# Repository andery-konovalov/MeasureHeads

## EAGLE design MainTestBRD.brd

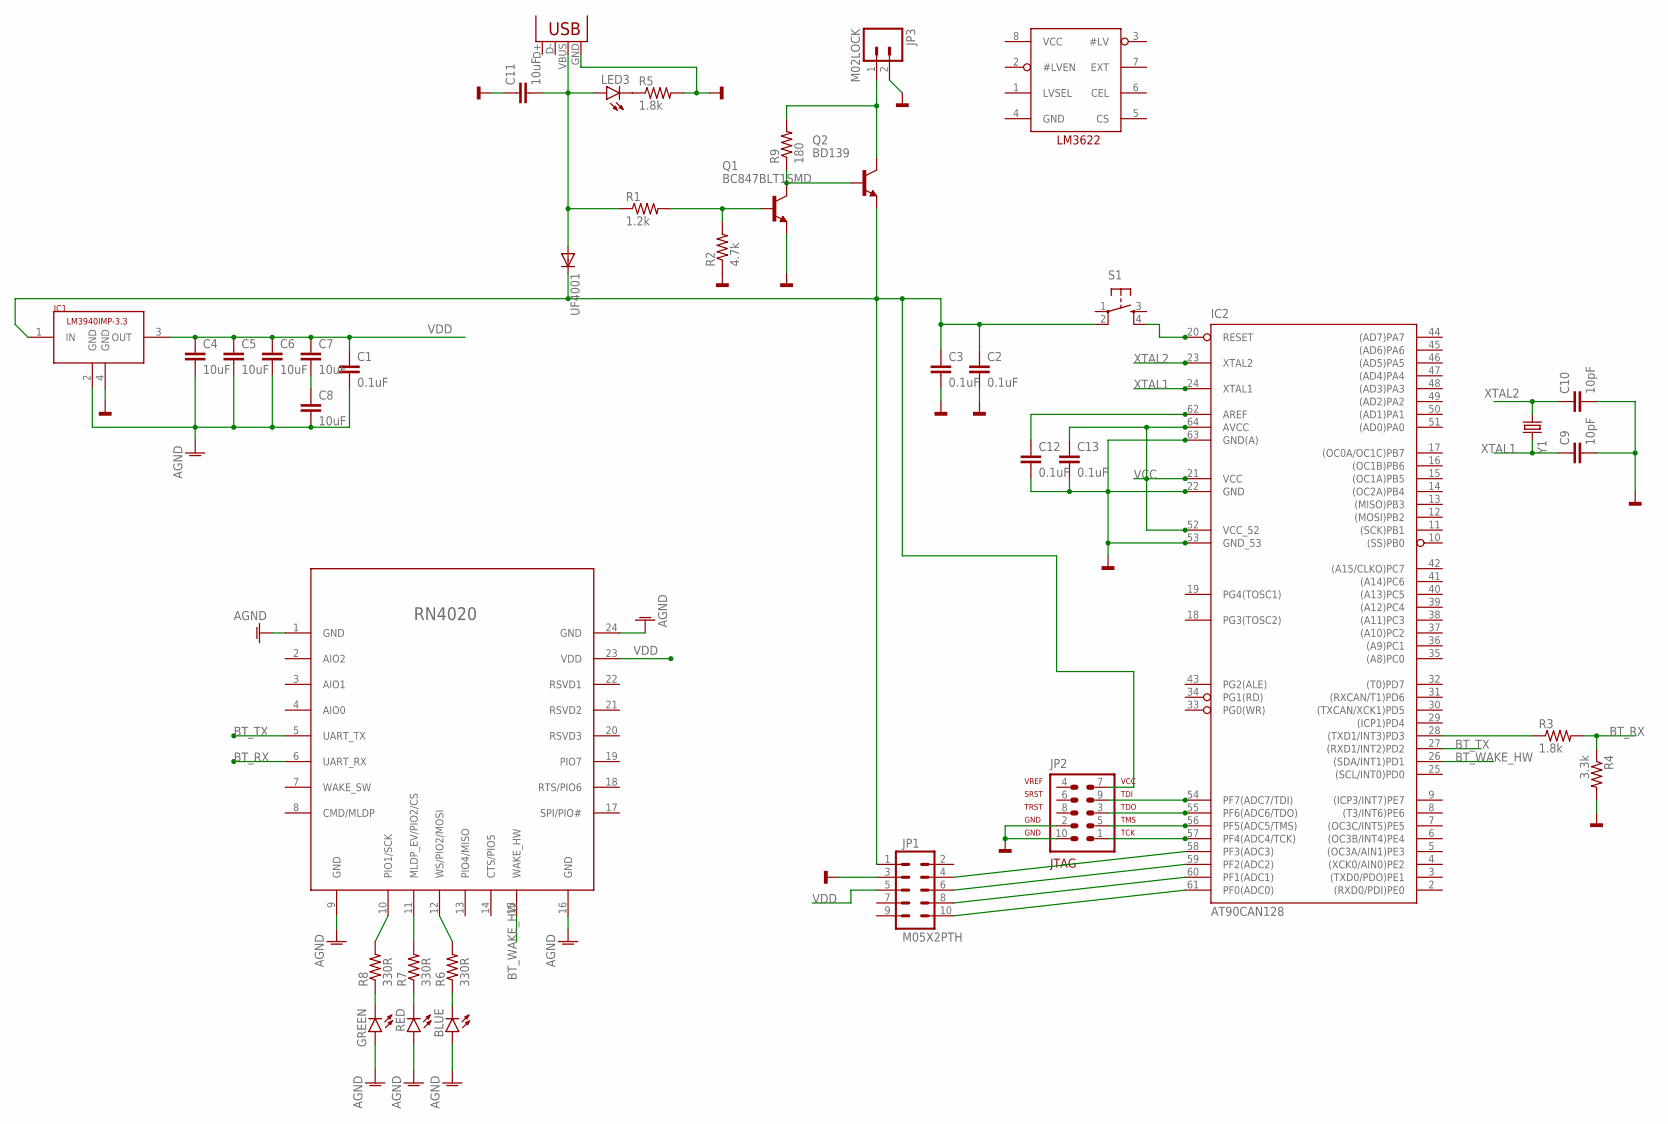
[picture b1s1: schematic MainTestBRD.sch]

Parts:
BLUE: LED1206; LED-1206
C1, C2, C3, C12, C13: 0.1uF; 1206
C4, C5, C6, C7, C8, C11: 10uF; 1206
C9, C10: 10pF; 1206
GREEN: LED1206; LED-1206
IC1: LM3940IMP-3.3; SOT223
IC2: AT90CAN128; TQFP64
JP1: M05X2PTH; AVR_ICSP
JP2: AVR-JTAG-10
JP3: M02LOCK; 1X02_LOCK
JP4: USB-B; USB-B-PTH
LED3: LED1206; LED-1206
Q1: BC847BLT1SMD; SOT23
Q2: BD139; TO126
R1: 1.2k; 0603-RES
R2: 4.7k; 0603-RES
R3, R5: 1.8k; 0603-RES
R4: 3.3k; 0603-RES
R6, R7, R8: 330R; 0603-RES
R9: 180; 0603-RES
RED: LED1206; LED-1206
S1: TAC_SWITCHPTH; TACTILE-PTH
U$1: LM3622; SO08
U$2: RN4020
UF4001: DIODE-DO41-7.6; DO41-7.6
Y1: CRYSTALHC49UV; HC49U-V

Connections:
AGND: BLUE.A, C1.2, C4.2, C5.2, C6.2, C8.2, GREEN.A, IC1.2 (GND), RED.A, U$2.1 (GND), U$2.9 (GND), U$2.16 (GND), U$2.24 (GND)
BT_RX: R3.2, R4.1, U$2.6 (UART_RX)
BT_TX: IC2.27 ((RXD1/INT2)PD2), U$2.5 (UART_TX)
BT_WAKE_HW: IC2.26 ((SDA/INT1)PD1), U$2.15 (WAKE_HW)
GND: C2.2, C3.2, C9.2, C10.2, C11.1, C12.2, C13.2, IC1.4 (GND), IC2.22 (GND), IC2.53 (GND_53), IC2.63 (GND(A)), JP1.3, JP2.2, JP2.10, JP3.2, JP4.GND, Q1.2 (E), R2.1, R4.2, R5.2
unnamed: R6.2, U$2.12 (WS/PIO2/MOSI)
unnamed: R8.2, U$2.10 (PIO1/SCK)
unnamed: IC2.28 ((TXD1/INT3)PD3), R3.1
unnamed: BLUE.C, R6.1
unnamed: R7.2, U$2.11 (MLDP_EV/PIO2/CS)
unnamed: IC2.57 (PF4(ADC4/TCK)), JP2.1
unnamed: R7.1, RED.C
unnamed: C7.2, C8.1
unnamed: IC2.56 (PF5(ADC5/TMS)), JP2.5
unnamed: GREEN.C, R8.1
unnamed: IC2.55 (PF6(ADC6/TDO)), JP2.3
unnamed: IC2.54 (PF7(ADC7/TDI)), JP2.9
unnamed: IC2.20 (RESET), S1.4
unnamed: Q1.1 (B), R1.2, R2.2
unnamed: C12.1, IC2.62 (AREF)
unnamed: IC2.61 (PF0(ADC0)), JP1.10
unnamed: C11.2, JP4.VBUS, LED3.A, R1.1, UF4001.A
unnamed: Q1.3 (C), Q2.3 (B), R9.1
unnamed: IC2.60 (PF1(ADC1)), JP1.8
unnamed: LED3.C, R5.1
unnamed: IC2.59 (PF2(ADC2)), JP1.6
unnamed: IC2.58 (PF3(ADC3)), JP1.4
unnamed: JP3.1, Q2.2 (C), R9.2
VCC: C2.1, C3.1, C13.1, IC1.1 (IN), IC2.21 (VCC), IC2.52 (VCC_52), IC2.64 (AVCC), JP1.1, JP2.7, S1.2, UF4001.C
VDD: C1.1, C4.1, C5.1, C6.1, C7.1, IC1.3 (OUT), JP1.5, U$2.23 (VDD)
XTAL1: C9.1, IC2.24 (XTAL1), Y1.2
XTAL2: C10.1, IC2.23 (XTAL2), Y1.1

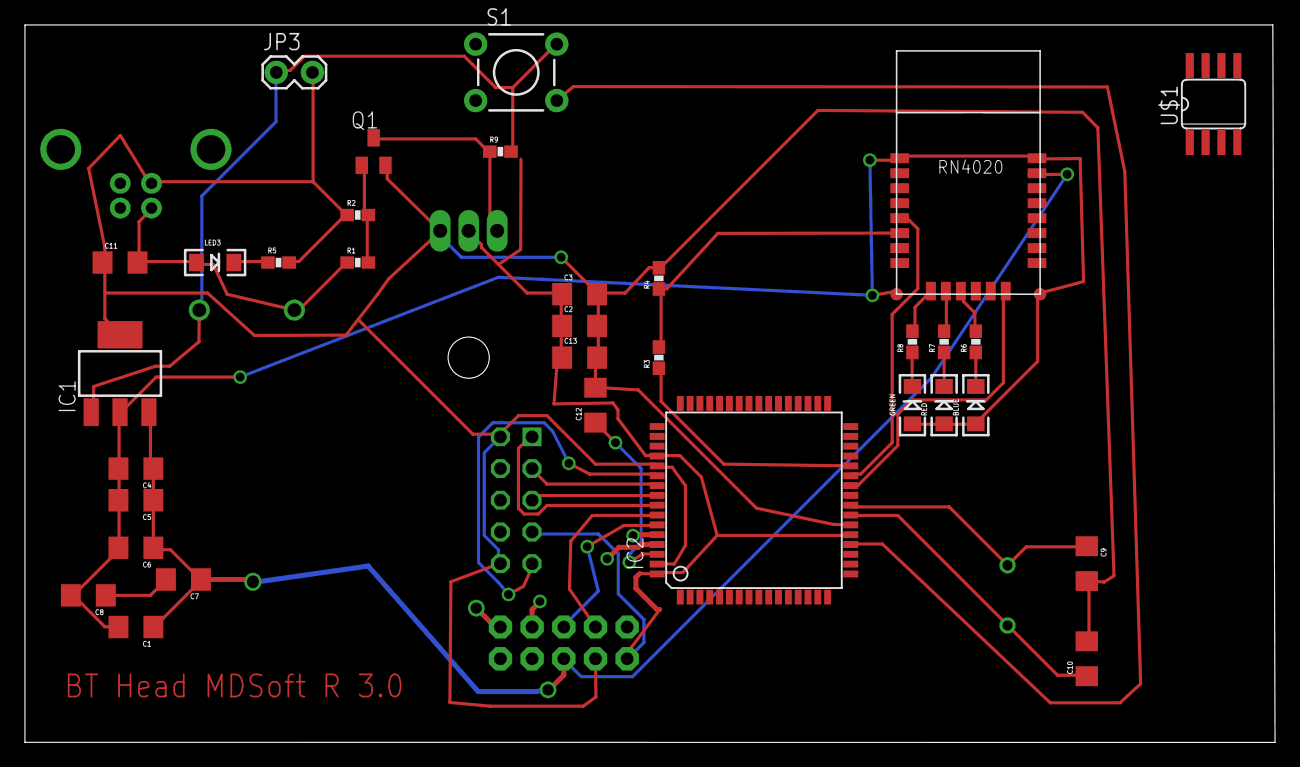
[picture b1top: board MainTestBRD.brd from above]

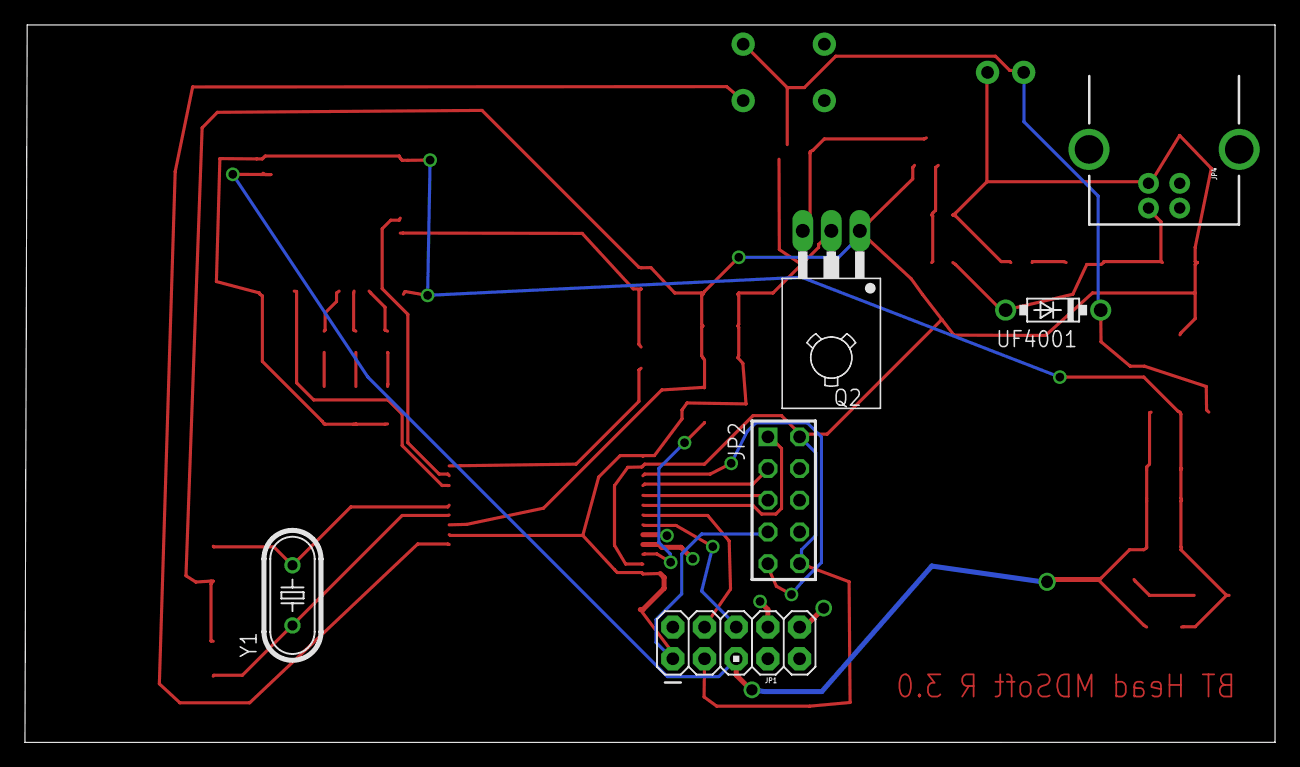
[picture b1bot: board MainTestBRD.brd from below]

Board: 2 copper layers, 100.2 x 57.5 mm, 39 parts (6 on the bottom side), 32 nets.

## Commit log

2014-10-06 board
2014-10-07 intermedate variant
2014-10-25 other pinouts
2014-10-29 additional pin outs added
2014-10-30 new power led
2014-10-30 new usb connector
2014-12-11 новая версия
2014-12-15 new implementation
2015-01-01 new version
2015-01-12 DTA143ZKA needs

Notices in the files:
parts and their libraries:
SparkFun-LED: Licensing: Creative Commons ShareAlike 4.0 International - https://creativecommons.org/licenses/by-sa/4.0
